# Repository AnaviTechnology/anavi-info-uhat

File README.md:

# ANAVI Info uHAT

ANAVI Info uHAT is an open source hardware Raspberry Pi uHAT (add-on board) for rapid prototyping of Internet of Things (IoT) powered by free and open source software. It features:

* 3 Buttons
* Red and green indication LEDs
* Slot of mini OLED I2C display
* Slots for up to 3 plug and play I2C sensors for temperature, barometric pressure, humidity and light
* UART (Universal asynchronous receiver/transmitter) pins for debugging

# Safety Information

## English

### Warnings

* This product shall only be connected to a compatible Raspberry Pi.

### Instructions for safe use

* Do not expose this product to water or moisture, and do not place it on a conductive surface whilst in operation.
* Do not expose this product to heat from any source; it is designed for reliable operation at normal room temperatures.
* Take care while handling this product to avoid mechanical or electrical damage to the printed circuit board and connectors.
* Avoid handling this product while it is powered. Only handle by the edges to minimize the risk of electrostatic discharge damage.

## Deutsch

### Achtung

* Dieses Produkt darf nur mit einem kompatiblen Raspberry Pi verbunden werden.

### Anweisungen für die sichere Verwendung

* Setzen Sie dieses Produkt nicht Wasser oder Feuchtigkeit aus und stellen Sie es während des Betriebs nicht auf eine leitfähige Oberfläche.
* Setzen Sie dieses Produkt keiner Wärmequelle aus. Es ist für einen zuverlässigen Betrieb bei normalen Raumtemperaturen ausgelegt.
* Seien Sie vorsichtig beim Umgang mit diesem Produkt, um mechanische oder elektrische Schäden an der Leiterplatte und den Anschlüssen zu vermeiden.
* Vermeiden Sie die Handhabung dieses Produkts während der Stromversorgung. Produkt nur an den Rändern anfassen, um das Risiko von elektrostatischen Entladungsschäden zu minimieren.

# License

The project is released under the [Creative Commons Attribution-ShareAlike 4.0 International (CC BY-SA 4.0)](https://creativecommons.org/licenses/by-sa/4.0/).

Note: This is a human-readable summary of (and not a substitute for) the [license](https://creativecommons.org/licenses/by-sa/4.0/legalcode).

You are free to:

Share — copy and redistribute the material in any medium or format Adapt — remix, transform, and build upon the material for any purpose, even commercially. The licensor cannot revoke these freedoms as long as you follow the license terms. Under the following terms:

Attribution — You must give appropriate credit, provide a link to the license, and indicate if changes were made. You may do so in any reasonable manner, but not in any way that suggests the licensor endorses you or your use. ShareAlike — If you remix, transform, or build upon the material, you must distribute your contributions under the same license as the original. No additional restrictions — You may not apply legal terms or technological measures that legally restrict others from doing anything the license permits. Notices:

You do not have to comply with the license for elements of the material in the public domain or where your use is permitted by an applicable exception or limitation. No warranties are given. The license may not give you all of the permissions necessary for your intended use. For example, other rights such as publicity, privacy, or moral rights may limit how you use the material.

You will have to provide a link to the original creator of the project http://www.anavi.technology on any documentation or website.

Credit can be attributed through a link to the creator website: http://www.anavi.technology

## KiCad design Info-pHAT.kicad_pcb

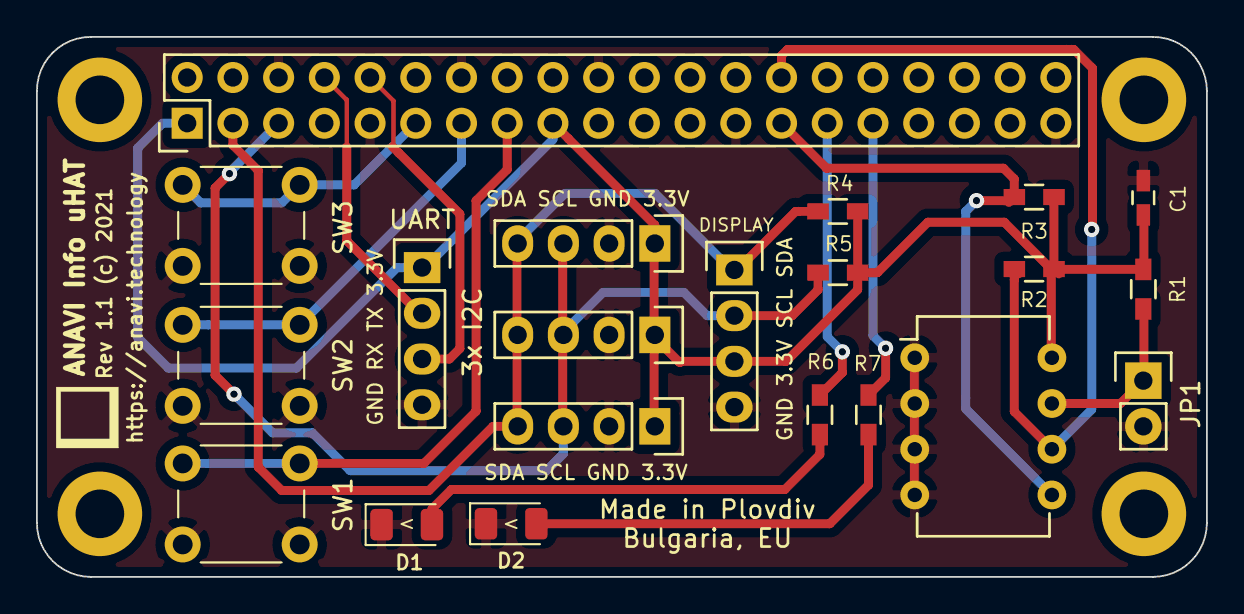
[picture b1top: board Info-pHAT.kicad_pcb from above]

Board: 2 copper layers, 65.0 x 30.0 mm, 25 parts (0 on the bottom side), 17 nets.

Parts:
C1: 0.1; C_0603_HandSoldering
D1: KP-3216EC; LED_1206_3216Metric
D2: KP-3216SGC; LED_1206_3216Metric
DISPLAY: DISPLAY1; Pin_Header_Straight_1x04
JP1: JUMPER; Pin_Header_Straight_1x02
R1: 1K; R_0603_HandSoldering
R2, R3, R4, R5: 4.7K; R_0603_HandSoldering
R6, R7: 270R; R_0603_HandSoldering
RASP_CONN1: Raspberry_PI; Pin_Header_Straight_2x20
REF1, REF2, REF3, REF4: MountingHole_2.7mm_M2.5_DIN965_Pad
SENS1, SENS2, SENS3: I2C_SENS_1; Pin_Header_Straight_1x04
SW1, SW2, SW3: SW_DIP_x01; SW_PUSH_6mm_h4.3mm
U1: CAT24C32WI-GT3; DIP-8_W7.62mm
UART: CONN_01X04; Pin_Header_Straight_1x04

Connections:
+3V3: C1.1, DISPLAY.3, R1.1, R2.1, R3.1, R4.1, R5.1, RASP_CONN1.1, RASP_CONN1.17, SENS1.1, SENS2.1, SENS3.1, U1.8, UART.1
+5V: RASP_CONN1.2, RASP_CONN1.4
/RXD: RASP_CONN1.10, UART.3
/TXD: RASP_CONN1.8, UART.2
GND: C1.2, D1.1, D2.1, DISPLAY.4, JP1.2, RASP_CONN1.6, RASP_CONN1.9, RASP_CONN1.14, RASP_CONN1.20, RASP_CONN1.25, RASP_CONN1.30, RASP_CONN1.34, RASP_CONN1.39, SENS1.2, SENS2.2, SENS3.2, SW1.2, SW2.2, SW3.2, U1.1, U1.2, U1.3, U1.4, UART.4
unnamed: D1.2, R6.1
unnamed: D2.2, R7.1
unnamed: JP1.1, R1.2, U1.7
unnamed: R2.2, RASP_CONN1.28, U1.6
unnamed: R3.2, RASP_CONN1.27, U1.5
unnamed: DISPLAY.1, R4.2, RASP_CONN1.3, SENS1.4, SENS2.4, SENS3.4
unnamed: DISPLAY.2, R5.2, RASP_CONN1.5, SENS1.3, SENS2.3, SENS3.3
unnamed: R6.2, RASP_CONN1.29
unnamed: R7.2, RASP_CONN1.31
unnamed: RASP_CONN1.11, SW3.1
unnamed: RASP_CONN1.13, SW2.1
unnamed: RASP_CONN1.15, SW1.1

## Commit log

2021-06-22 Info-pHAT.pro: Add LED D1 and D2
    Add indication LEDs D1 and D2.
2021-06-23 Info-pHAT.kicad_pcb: Update labels
    Update labels and adjust positions.
2021-07-05 Info-pHAT.kicad_pcb: Add a label
    Add a label for the direction of the LEDs.
2021-12-30 README.md: Rename for pHAT to uHAT
    Rename the project from ANAVI Info pHAT to ANAVI Info uHAT
    because it covers all Raspberry Pi requirements for uHAT, a.k.a.
    micro Hardware Attached on Top.
2022-02-02 Info-pHAT.kicad_pcb: Add assembly details
    Add details for the assembly to the fabrication layer.
2022-04-11 README.md: Safety information
    Add safety information for ANAVI Info uHAT.

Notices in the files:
Info-pHAT.kicad_pcb:
Rev 1.1 (c) 2021
